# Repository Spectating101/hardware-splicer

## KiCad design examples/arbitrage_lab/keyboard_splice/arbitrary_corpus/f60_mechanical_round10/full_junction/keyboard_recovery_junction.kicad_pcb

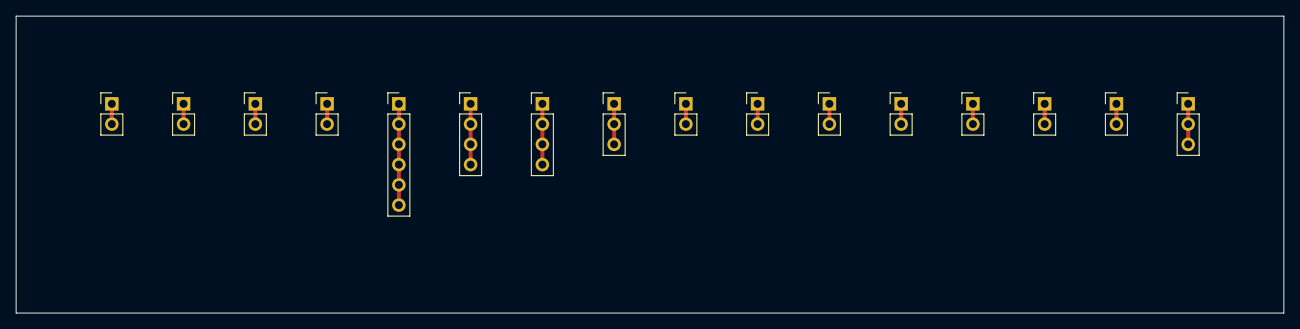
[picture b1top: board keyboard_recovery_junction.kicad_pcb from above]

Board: 2 copper layers, 159.0 x 37.2 mm, 16 parts (0 on the bottom side), 16 nets.

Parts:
J01, J02, J03, J04, J09, J10, J11, J12, J13, J14, J15: PinHeader_1x02_P2.54mm_Vertical
J05: PinHeader_1x06_P2.54mm_Vertical
J06, J07: PinHeader_1x04_P2.54mm_Vertical
J08, J16: PinHeader_1x03_P2.54mm_Vertical

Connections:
HARNESS_NET_01: J01.1, J01.2
HARNESS_NET_02: J02.1, J02.2
HARNESS_NET_03: J03.1, J03.2
HARNESS_NET_04: J04.1, J04.2
HARNESS_NET_05: J05.1, J05.2, J05.3, J05.4, J05.5, J05.6
HARNESS_NET_06: J06.1, J06.2, J06.3, J06.4
HARNESS_NET_07: J07.1, J07.2, J07.3, J07.4
HARNESS_NET_08: J08.1, J08.2, J08.3
HARNESS_NET_09: J09.1, J09.2
HARNESS_NET_10: J10.1, J10.2
HARNESS_NET_11: J11.1, J11.2
HARNESS_NET_12: J12.1, J12.2
HARNESS_NET_13: J13.1, J13.2
HARNESS_NET_14: J14.1, J14.2
HARNESS_NET_15: J15.1, J15.2
HARNESS_NET_16: J16.1, J16.2, J16.3

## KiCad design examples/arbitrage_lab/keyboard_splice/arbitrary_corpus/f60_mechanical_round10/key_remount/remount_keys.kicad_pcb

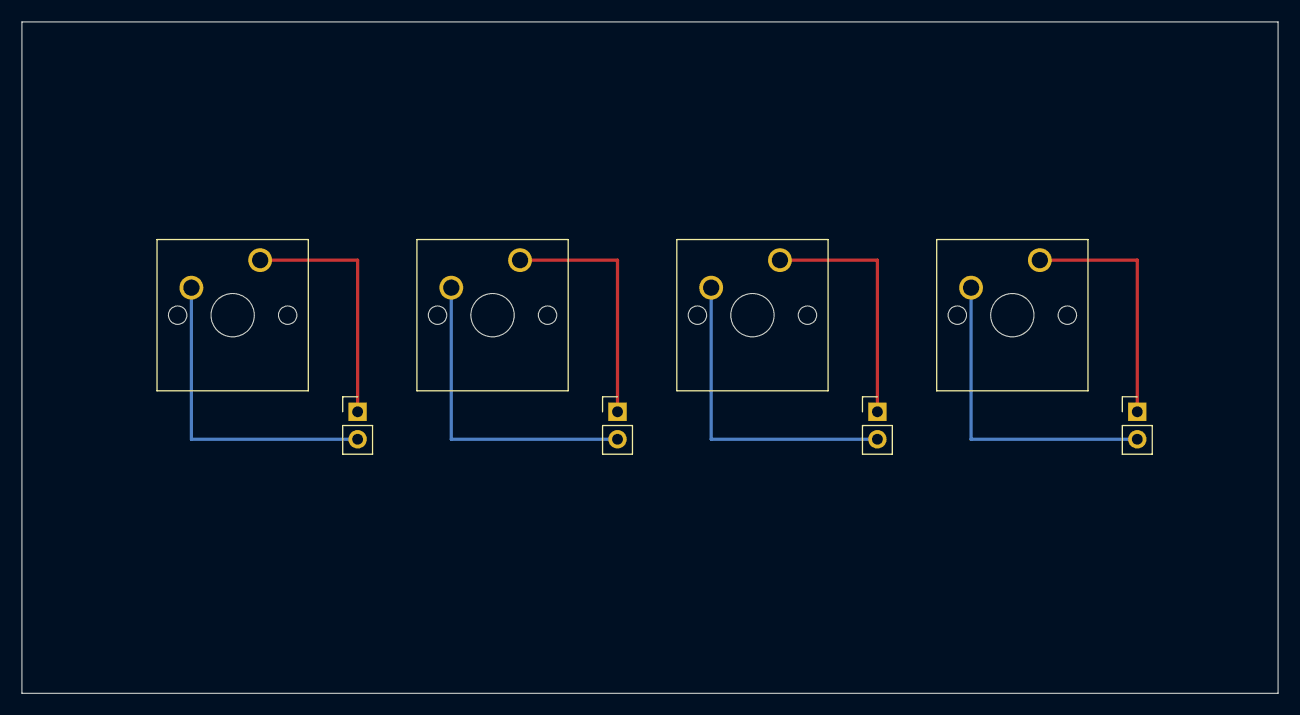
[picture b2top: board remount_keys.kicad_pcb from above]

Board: 2 copper layers, 116.0 x 62.0 mm, 8 parts (0 on the bottom side), 8 nets.

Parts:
J1, J2, J3, J4: PinHeader_1x02_P2.54mm_Vertical
SW1, SW2, SW3, SW4: SW_Cherry_MX_1.00u_PCB

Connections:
KEY01_CONTACT1: J1.1, SW1.1
KEY01_CONTACT2: J1.2, SW1.2
KEY02_CONTACT1: J2.1, SW2.1
KEY02_CONTACT2: J2.2, SW2.2
KEY03_CONTACT1: J3.1, SW3.1
KEY03_CONTACT2: J3.2, SW3.2
KEY04_CONTACT1: J4.1, SW4.1
KEY04_CONTACT2: J4.2, SW4.2
